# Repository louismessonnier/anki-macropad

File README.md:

# Anki Macropad

A custom 6-key macropad designed for use with [Anki](https://apps.ankiweb.net/), a spaced repetition flashcard application. The macropad features an RP2040 microcontroller directly on the PCB, a custom case, and QMK firmware.

---

## Table of Contents

* [Overview](#overview)
* [Planning](#planning)
* [Layout Design](#layout-design)
* [PCB Design](#pcb-design)
* [Firmware](#firmware)

---

## Overview

Rather than using a pre-built microcontroller board such as a Raspberry Pi Pico, this macropad integrates an RP2040 MCU directly onto a custom PCB. This approach allows full control over board dimensions, USB port placement, and component layout — and presents a more complete hardware design challenge.

The macropad is designed around the Anki study workflow: rating flashcards (Again / Hard / Good / Easy), flipping cards to reveal the answer, and editing cards on the fly.

**Tools used:** KiCad (schematic & PCB), SolidWorks (case), QMK MSYS (firmware), JLCPCB (PCB fabrication)

---

## Planning

### Process

The overall project plan was structured as follows:

1. **Preparation** — collect resources, create GitHub repository, research PCB design
2. **Layout design** — identify macropad goals, design key layout
3. **PCB design** — schematic, footprint assignment, PCB layout, trace routing, DRC, export production files
4. **Order PCB** from JLCPCB
5. **Case design** — generate plate, design top and bottom case in SolidWorks, 3D print
6. **Firmware** — configure QMK, flash firmware
7. **Assembly** — solder switches, assemble PCB with case

### Major Resources

|Resource|Description|
|-|-|
|[Hardware Design with RP2040](https://pip-assets.raspberrypi.com/categories/814-rp2040/documents/RP-008279-DS-1-hardware-design-with-rp2040.pdf)|Official Raspberry Pi documentation covering hardware design requirements for the RP2040 on a custom PCB, including a minimal design example.|
|[Joe Scotto — PCB Design Playlist](https://www.youtube.com/playlist?list=PLBD2IS_t_iWZDMdG_ZF57x9Ebm3kxKqxF) and [GitHub Library](https://github.com/joe-scotto/scottokeebs/tree/main)|Videos covering mechanical keyboard PCB design in KiCad, including designs using an STM32 MCU directly on a PCB. Used for understanding KiCad workflow and as a reference for footprints.|
|[Mechanical Keyboard PCB Design Guide — PCBSync](https://pcbsync.com/mechanical-keyboard-pcb-design/)|Broad overview of the keyboard PCB design process, covering matrix design, schematic structure, and routing guidelines.|
|[Hardware Design with RP2040 — DigiKey YouTube](https://www.youtube.com/watch?v=kcwvuwetgEQ&t=7s)|Video covering key aspects of designing, fabricating, and testing a custom PCB with an RP2040.|
|[QMK Firmware Documentation](https://docs.qmk.fm/)|Official documentation for QMK firmware used to configure and build the keyboard firmware.|

---

## Layout Design

### Goals

The macropad is designed around the core Anki study workflow:

* **Rate a card:** Again (1), Hard (2), Good (3), Easy (4)
* **Flip a card:** Spacebar
* **Edit a card:** E

After testing different configurations on a standard keyboard, the following layout was chosen. The four rating keys are in the top row. A wide 3U key on the bottom acts as the spacebar/flip key, and the edit key sits to the right as a thumb key.

---

## PCB Design

### Why RP2040

The RP2040 was chosen as the MCU for two main reasons:

1. **Design flexibility** — placing the microcontroller directly on the PCB means the USB port can be positioned freely and no bulky external microcontroller board is required, allowing a more compact and clean design.
2. **Challenge** — designing the supporting hardware around the RP2040 from scratch is a more complete engineering exercise than simply plugging in a Pico.

### Hardware Components

The following components were selected to support the RP2040, largely following the minimal design example in the official hardware documentation.

**Power**

|Component|Quantity|Use|
|-|-|-|
|USB-C Receptacle (USB2.0, 14P)|1|5V input power via VBUS|
|5.1kΩ pull-down resistors (CC1/CC2)|2|Signal to USB-C power source that a device is connected|
|NCP1117-3.3 LDO (SOT-223)|1|Convert 5V to 3.3V|
|10µF capacitors (0805)|2|Input and output decoupling for LDO|
|USBLC6-2SC6 ESD protection (SOT-23-6)|1|Protect against ESD on USB lines|
|100nF decoupling capacitors (0402)|9|Filter power supply noise for RP2040 power pins|
|1µF capacitors (0402)|2|Stabilize internal 1.1V voltage regulator (VREG_IN and VREG_OUT)|

**Flash Storage**

|Component|Quantity|Use|
|-|-|-|
|W25Q128JVS QSPI Flash (SOIC-8)|1|Store program code for RP2040 to boot from|
|100nF capacitor (0402)|1|Decoupling for flash VCC|
|PTS810 SJK 250 SMTR LFS tactile button|1|BOOTSEL button — hold while powering on to enter USB bootloader mode|
|1kΩ resistor (0402)|1|Series resistor on QSPI_SS for BOOTSEL circuit|
|10kΩ resistor (0402)|1|Pull-up resistor for BOOTSEL circuit|

**Crystal Oscillator**

|Component|Quantity|Use|
|-|-|-|
|ABM8-272-T3 12MHz crystal|1|Stable external clock source|
|15pF load capacitors (0402)|2|Provide the 10pF effective load capacitance required by the crystal|
|1kΩ series resistor on XOUT (0402)|1|Prevents crystal overdrive at 3.3V IOVDD|

**USB I/O**

|Component|Quantity|Use|
|-|-|-|
|27Ω series resistors (0402)|2|USB impedance matching on USB_DP and USB_DM|

**Key Matrix**

|Component|Quantity|Use|
|-|-|-|
|MX-compatible key switches|6|Input keys|
|1N4148W diodes (SOD-123)|6|Anti-ghosting, enables N-key rollover|

### Schematic Design

#### RP2040 Hardware

The RP2040 schematic is divided into four sections:

* **Controller** — RP2040 MCU, decoupling capacitors, internal voltage regulator capacitors, USB series termination resistors
* **Crystal Oscillator** — 12MHz crystal with load capacitors and XOUT series resistor
* **Flash Storage** — W25Q128JVS QSPI flash with decoupling cap and BOOTSEL button circuit
* **Connector** — USB-C connector, NCP1117 LDO voltage regulator, ESD protection (USBLC6-2SC6)

The ESD protection component was added based on the recommendation of the PCBSync guide and was not present in the minimal design example.

#### Keyboard Matrix

A 3-row × 4-column matrix is used, even though the macropad only has 6 keys. Using a matrix (rather than one GPIO per switch) is standard practice and allows diodes to be included. The diodes solve the ghosting problem — without them, pressing three keys in an L-shaped pattern can falsely register the fourth corner key. The diodes enforce one-way current flow, which also enables N-key rollover.

GPIO assignments:

* **Rows:** GPIO0 (Row 0), GPIO1 (Row 1), GPIO2 (Row 2)
* **Columns:** GPIO24 (Col 0), GPIO25 (Col 1), GPIO6 (Col 2), GPIO7 (Col 3)

#### Full Schematic

The two modules above are combined on a single schematic sheet, along with mounting holes and power flags for VBUS and GND. GPIO row and column pin assignments were chosen based on the RP2040 footprint to minimise routing difficulty on the PCB layout.

### Footprint Assignment

Footprints for most components came from KiCad's built-in libraries. The following exceptions were used:

* **USB-C connector** — footprint from Joe Scotto's repository
* **Key switches** — footprint from the [marbastlib](https://github.com/ebastler/marbastlib) KiCad keyboard library
* **Matrix diodes** — SOD-123 footprint from Joe Scotto's repository
* **Resistors and capacitors** — 0402 footprints, same as used in the minimal design example

### Board Configuration

The board was configured in KiCad's Board Setup to match JLCPCB's manufacturing capabilities.

<details>
<summary>JLCPCB Manufacturing Capabilities (click to expand)</summary>

**PCB Specifications**

* Layer count: 2
* Material: FR-4, dielectric constant 4.5
* Thickness: 1.6mm
* Copper weight: 1 oz
* Surface finish: Leaded HASL

**Drilling**

* Drill diameter: 0.15–6.3mm
* Min via hole / diameter: 0.15mm / 0.25mm
* Via hole-to-hole spacing: 0.2mm

**Traces**

* Min track width / spacing (1 oz): 0.10 / 0.10mm
* PTH annular ring: ≥0.25mm
* Pad to track clearance: 0.1mm

**Soldermask**

* Expansion: 1:1
* Bridge: 0.10mm

**Silkscreen**

* Minimum line width: 0.15mm
* Minimum text height: 1.0mm

</details>

**KiCad Board Setup**

|Parameter|Value|Justification|
|-|-|-|
|Copper layers|2|Sufficient for this design; cheapest option|
|Board thickness|1.6mm|Standard|
|Copper finish|HAL SnPb|Standard, cheap|
|Solder mask expansion|0mm|JLCPCB 1:1 expansion|
|Solder mask min web width|0.10mm|JLCPCB spec|
|Minimum clearance|0.10mm|JLCPCB minimum|
|Minimum track width|0.10mm|JLCPCB minimum|
|Minimum annular width|0.25mm|JLCPCB PTH annular ring spec|
|Copper to hole clearance|0.25mm|Matches minimal design example|
|Copper to edge clearance|0.5mm|Matches Joe Scotto template|
|Minimum drill size|0.15mm|JLCPCB minimum|
|Hole to hole clearance|0.20mm|JLCPCB spec|
|Minimum text height|1.0mm|JLCPCB spec|
|Minimum text thickness|0.15mm|JLCPCB spec|

**Net Classes**

|Name|Clearance|Track Width|Via Size|Via Hole|DP Width|DP Gap|
|-|-|-|-|-|-|-|
|Default|0.15mm|0.2mm|0.45mm|0.3mm|0.2mm|0.25mm|
|Power|0.2mm|0.4mm|0.45mm|0.3mm|0.2mm|0.25mm|
|USB Data|0.2mm|0.2mm|0.45mm|0.3mm|0.8mm|0.16mm|

Via sizes were chosen to maintain a 0.25mm annular ring (JLCPCB minimum): annular ring = (via diameter − hole diameter) / 2 = (0.45 − 0.3) / 2 = 0.075mm... actually 0.75mm via size with 0.25mm drill was the final choice.

The USB Data differential pair width (0.8mm) and gap (0.16mm) were calculated using the KiCad PCB Calculator transmission lines tool to achieve the 90Ω characteristic impedance required by the USB specification, using the JLCPCB 1.6mm FR4 stackup parameters (Er = 4.5, copper thickness = 0.035mm).

### PCB Layout

The RP2040 and all its supporting components are placed on the back of the board. The switches are on the front, with their diodes adjacent on the back. This keeps the front of the board clean and follows the recommendations in the hardware documentation.

Key layout decisions:

* Decoupling capacitors placed as close as possible to the RP2040's power pins
* 1µF VREG capacitors (C8, C10) placed directly next to VREG_IN (pin 45) and VREG_OUT (pin 44)
* QSPI flash connected to the RP2040 with short, direct traces
* R1 and R2 (BOOTSEL resistors) placed close to the flash chip
* USB series termination resistors (R3, R4) placed close to the RP2040's USB pins

### Trace Routing

Routing was done almost entirely on the back copper layer, where the components are located. Filled copper zones were used for power distribution:

* **Front (F.Cu):** Full-board ground fill
* **Back (B.Cu):** +3V3 fill covering most of the board; smaller +1V1 fill under the RP2040; three local ground fills

For the USB data lines, a solid ground fill is placed directly below the traces for the full length of the track, as required by the hardware documentation for the transmission lines to function correctly. Crystal traces were kept short and routed directly to the MCU pins.

### Manufacturing

The board was ordered from JLCPCB with SMT assembly (PCBA) for all surface-mount components except the MX switches, which were soldered by hand after the boards arrived. The minimum order was 5 PCBs.

---

## Firmware

The firmware is built using [QMK](https://qmk.fm/). See [`firmware/README.md`](firmware/README.md) for build and flash instructions.

The keymap assigns the following keys:

|Physical Key|Keycode|Anki Function|
|-|-|-|
|Again|`1`|Rate card: Again|
|Hard|`2`|Rate card: Hard|
|Good|`3`|Rate card: Good|
|Easy|`4`|Rate card: Easy|
|Edit|`E`|Edit current card|
|Show Answer|`Space`|Flip card / show answer|

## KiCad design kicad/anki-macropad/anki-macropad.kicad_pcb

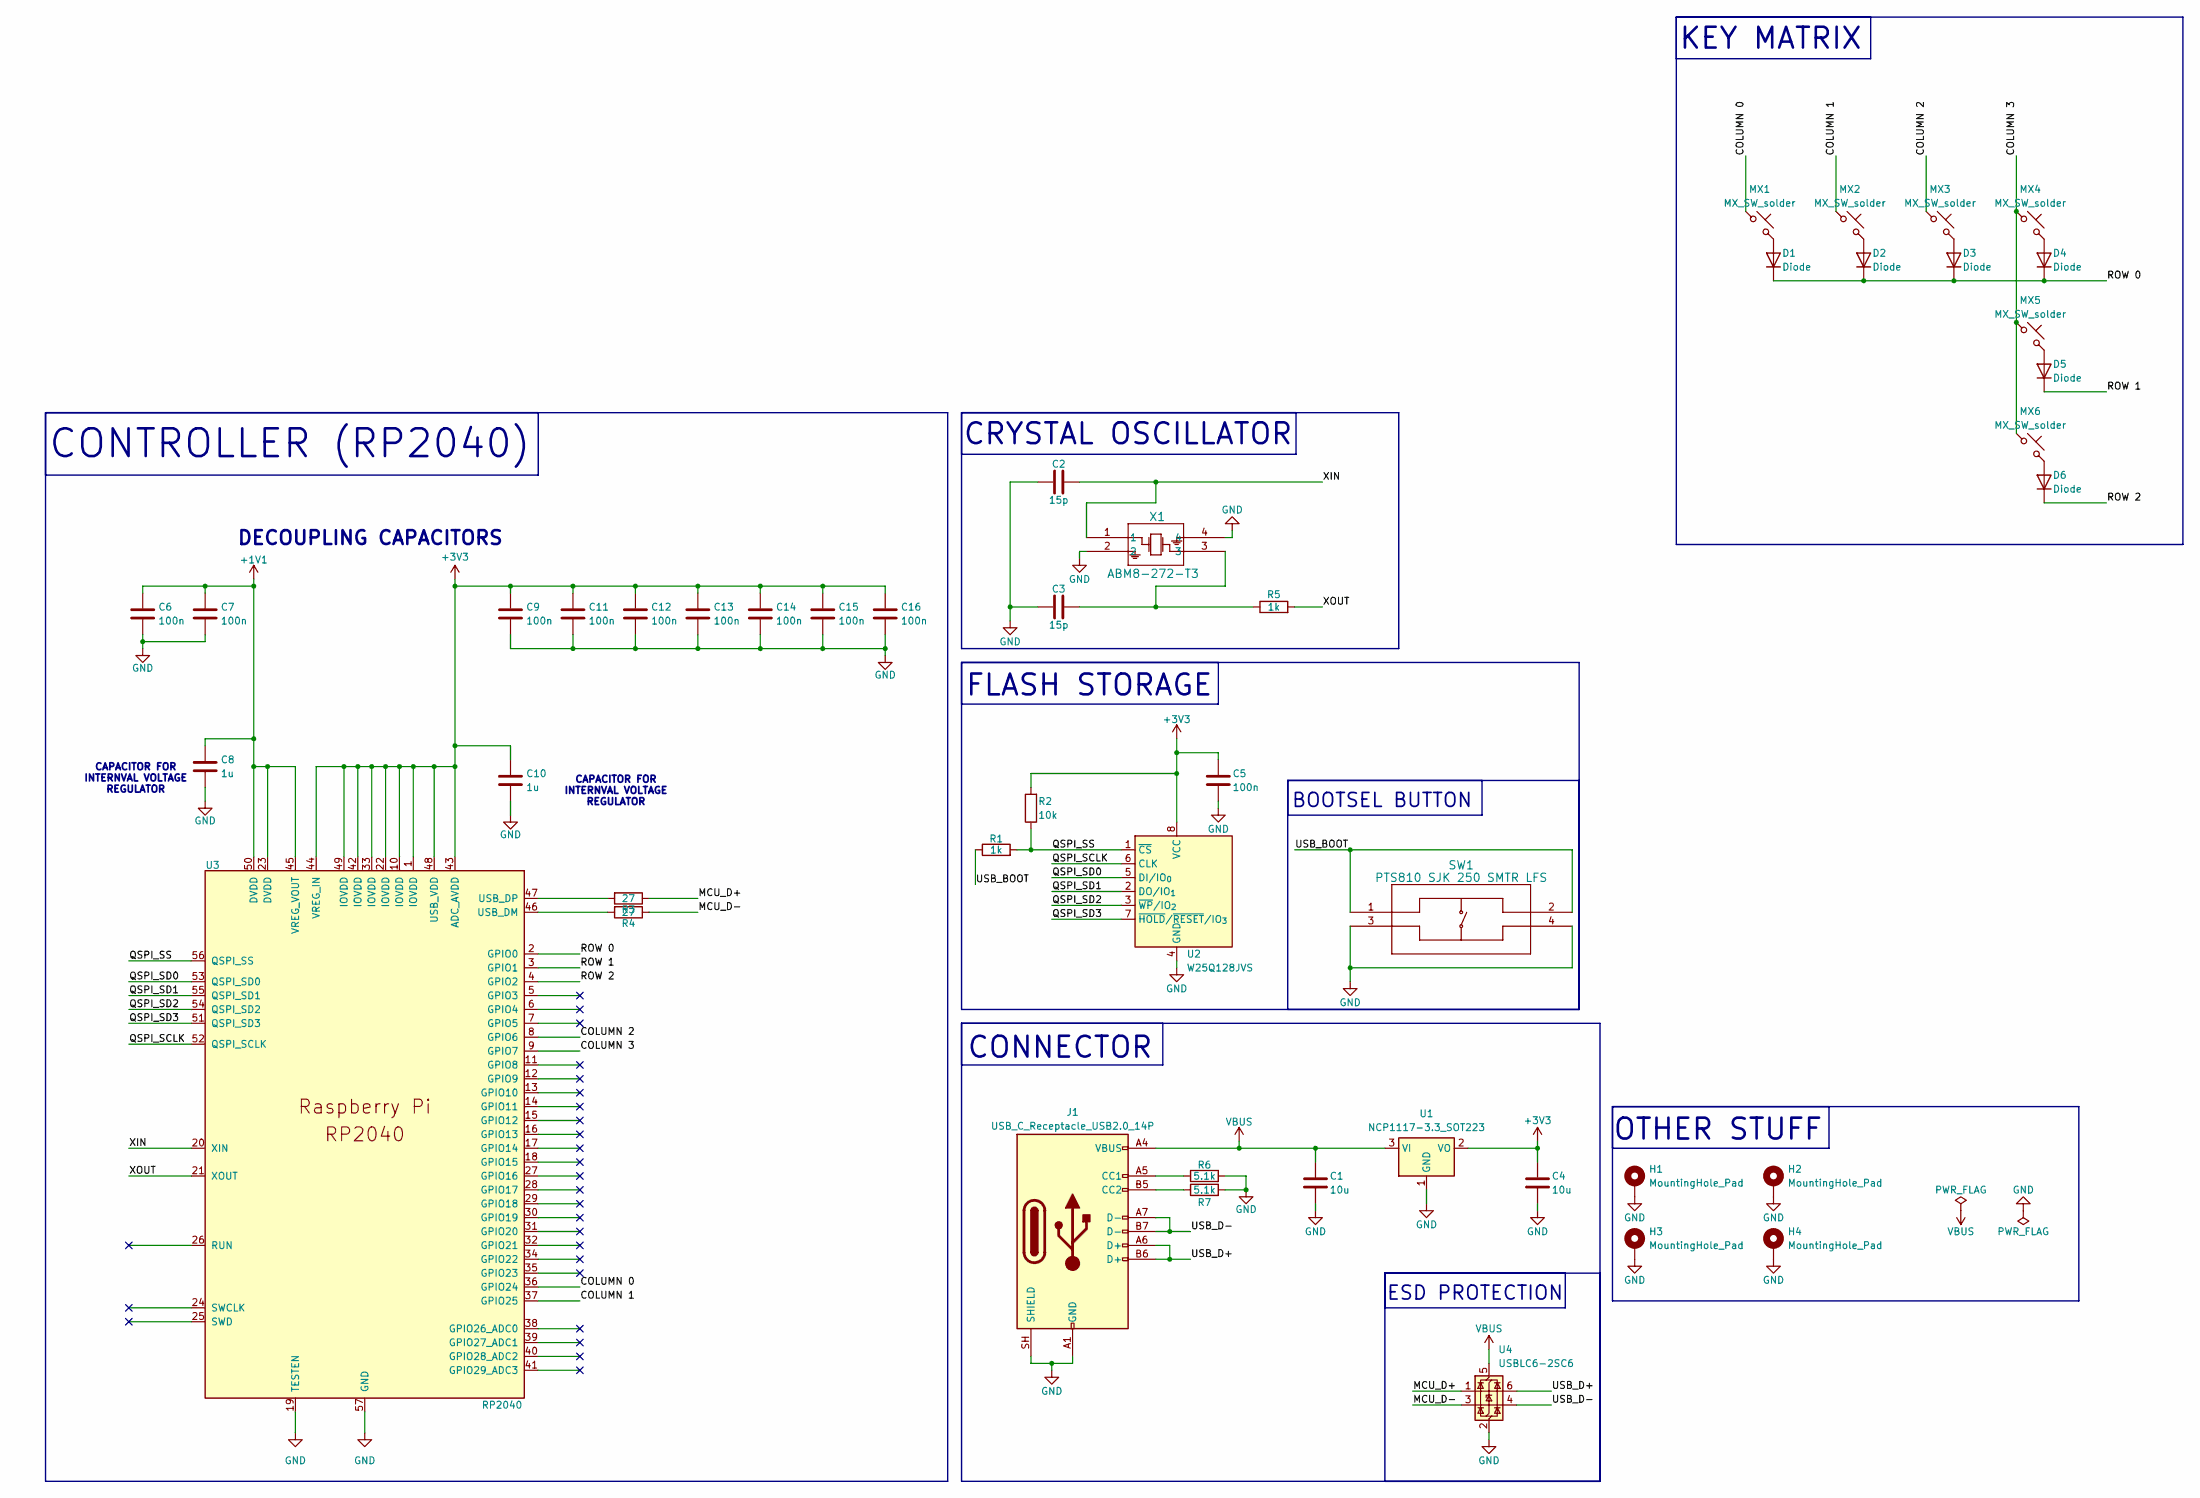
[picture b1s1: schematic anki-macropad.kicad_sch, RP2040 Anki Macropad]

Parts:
C1, C4: 10u; C_0805_2012Metric
C2, C3: 15p; C_0402_1005Metric
C5, C6, C7, C9, C11, C12, C13, C14, C15, C16: 100n; C_0402_1005Metric
C8, C10: 1u; C_0402_1005Metric
D1, D2, D3, D4, D5, D6: Diode; D_SOD-123
H1, H2, H3, H4: MountingHole_Pad; MountingHole_2.7mm_M2.5_Pad
J1: USB_C_Receptacle_USB2.0_14P; USB_C_HRO_TYPE-C-31-M-12
MX1, MX2, MX3, MX4, MX5, MX6: MX_SW_solder; SW_MX_1u
R1, R5: 1k; R_0402_1005Metric
R2: 10k; R_0402_1005Metric
R3, R4: 27; R_0402_1005Metric
R6, R7: 5.1k; R_0402_1005Metric
SW1: PTS810 SJK 250 SMTR LFS; PTS810_CNK
U1: NCP1117-3.3_SOT223; SOT-223-3_TabPin2
U2: W25Q128JVS; SOIC-8_5.3x5.3mm_P1.27mm
U3: RP2040; RP2040-QFN-56
U4: USBLC6-2SC6; SOT-23-6
X1: ABM8-272-T3; ABM8-272-T3_ABR

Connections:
+1V1: C6.1, C7.1, C8.1, U3.23 (DVDD), U3.45 (VREG_VOUT), U3.50 (DVDD)
+3V3: C4.1, C5.1, C9.1, C10.1, C11.1, C12.1, C13.1, C14.1, C15.1, C16.1, R2.2, U1.2 (VO), U2.8 (VCC), U3.1 (IOVDD), U3.10 (IOVDD), U3.22 (IOVDD), U3.33 (IOVDD), U3.42 (IOVDD), U3.43 (ADC_AVDD), U3.44 (VREG_IN), U3.48 (USB_VDD), U3.49 (IOVDD)
/COLUMN 0: MX1.1, U3.36 (GPIO24)
/COLUMN 1: MX2.1, U3.37 (GPIO25)
/COLUMN 2: MX3.1, U3.8 (GPIO6)
/COLUMN 3: MX4.1, MX5.1, MX6.1, U3.9 (GPIO7)
/MCU_D+: R3.1, U4.1 (I/O1)
/MCU_D-: R4.1, U4.3 (I/O2)
/QSPI_SCLK: U2.6 (CLK), U3.52 (QSPI_SCLK)
/QSPI_SD0: U2.5 (DI/IO_{0}), U3.53 (QSPI_SD0)
/QSPI_SD1: U2.2 (DO/IO_{1}), U3.55 (QSPI_SD1)
/QSPI_SD2: U2.3 (~WP/IO_{2}), U3.54 (QSPI_SD2)
/QSPI_SD3: U2.7 (~HOLD/~RESET/IO_{3}), U3.51 (QSPI_SD3)
/QSPI_SS: R1.2, R2.1, U2.1 (~CS), U3.56 (QSPI_SS)
/ROW 0: D1.1 (K), D2.1 (K), D3.1 (K), D4.1 (K), U3.2 (GPIO0)
/ROW 1: D5.1 (K), U3.3 (GPIO1)
/ROW 2: D6.1 (K), U3.4 (GPIO2)
/USB_BOOT: R1.1, SW1.1, SW1.2
/USB_D+: J1.A6 (D+), J1.B6 (D+), U4.6 (I/O1)
/USB_D-: J1.A7 (D-), J1.B7 (D-), U4.4 (I/O2)
/XIN: C2.2, U3.20 (XIN), X1.1
/XOUT: R5.2, U3.21 (XOUT)
GND: C1.2, C2.1, C3.1, C4.2, C5.2, C6.2, C7.2, C8.2, C9.2, C10.2, C11.2, C12.2, C13.2, C14.2, C15.2, C16.2, H1.1 (1_1), H2.1 (1_1), H3.1 (1_1), H4.1 (1_1), J1.A1 (GND), J1.A12 (GND), J1.B1 (GND), J1.B12 (GND), J1.S1, J1.SH (SHIELD), R6.2, R7.2, SW1.3, SW1.4, U1.1 (GND), U2.4 (GND), U3.19 (TESTEN), U3.57 (GND), U4.2 (GND), X1.2, X1.4
unnamed: C3.2, R5.1, X1.3
unnamed: D1.2 (A), MX1.2
unnamed: D2.2 (A), MX2.2
unnamed: D3.2 (A), MX3.2
unnamed: D4.2 (A), MX4.2
unnamed: D5.2 (A), MX5.2
unnamed: D6.2 (A), MX6.2
unnamed: J1.A5 (CC1), R6.1
unnamed: J1.B5 (CC2), R7.1
unnamed: R4.2, U3.46 (USB_DM)
unnamed: R3.2, U3.47 (USB_DP)
VBUS: C1.1, J1.A4 (VBUS), J1.A9 (VBUS), J1.B4 (VBUS), J1.B9 (VBUS), U1.3 (VI), U4.5 (VBUS)

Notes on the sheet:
CONTROLLER (RP2040)
OTHER STUFF
CAPACITOR FOR INTERNVAL VOLTAGE REGULATOR
CONNECTOR
KEY MATRIX
CRYSTAL OSCILLATOR
DECOUPLING CAPACITORS
BOOTSEL BUTTON
ESD PROTECTION
FLASH STORAGE

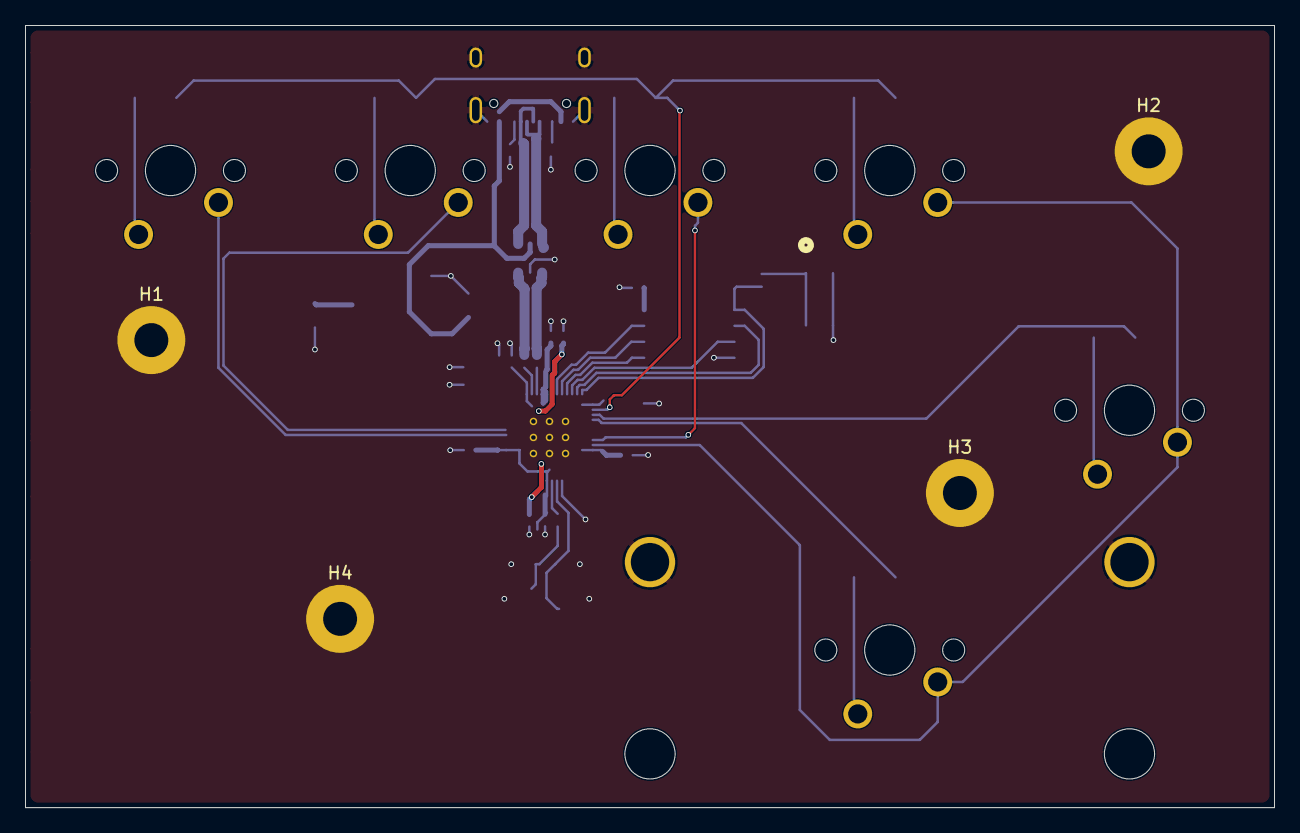
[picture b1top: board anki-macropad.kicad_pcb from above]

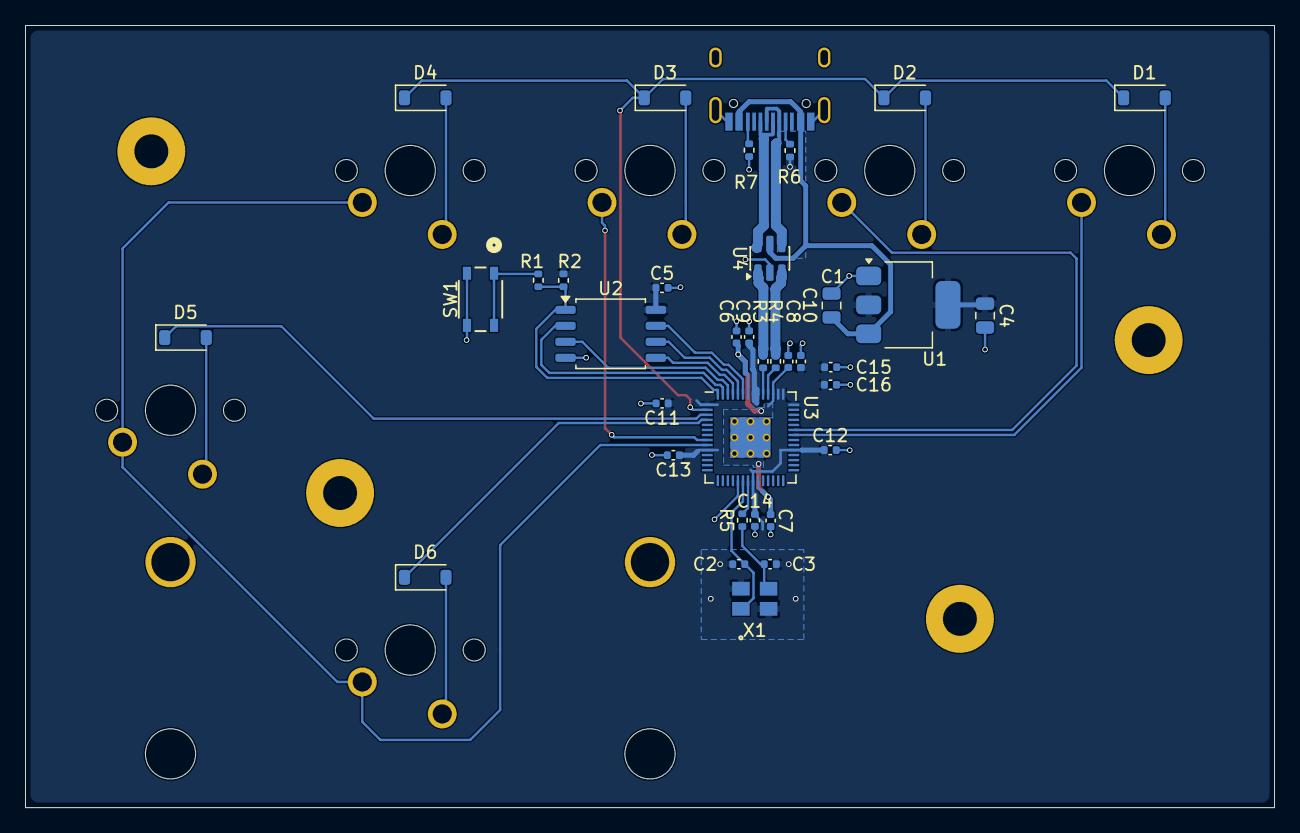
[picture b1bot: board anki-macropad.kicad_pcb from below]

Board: 2 copper layers, 99.2 x 62.1 mm, 46 parts (36 on the bottom side), 35 nets.

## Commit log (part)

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2026-06-03 Add project folder structure and various files
2026-06-04 Beginning schematic for anki macropad
2026-06-04 Working on schematic
2026-06-08 Finished schematic, started pcb
2026-06-10 Worked on PCB layout and traces
2026-06-10 Pretty much finished the PCB. Just need to go through DRC.
2026-06-11 Finished PCB design including DRC
2026-06-16 Made final touches to PCB. Ordered.
2026-06-17 Designed case for macropad
2026-06-17 made small edits to dimensions on kicad pcb
2026-06-17 v1 print files
2026-06-17 Print files
2026-06-17 small update
2026-06-18 updated gitignore
2026-06-18 added exploded view
2026-06-18 images of project
2026-06-18 name change
2026-06-18 removed, did not use
2026-06-18 exported schematic as pdf for project presentation
2026-06-18 images to present project
2026-06-21 images of v1 case print
2026-06-21 v2 case design
2026-06-23 v2 design of case completed
2026-06-23 v3 design of case completed
2026-06-23 completed second version of case design
2026-06-23 completed third version of case design
2026-06-25 created firmware for macropad
2026-06-25 finalized design for v2 case
2026-06-25 finalized design for v3 case
2026-06-27 file sent to printer for v2 and v3 case print
2026-06-27 images of pcb design
2026-06-30 added v3 image
2026-06-30 added v1 images
2026-06-30 added v2 images
2026-06-30 removed
2026-06-30 updated firmware readme
2026-06-30 updated main readme
2026-06-30 updated images
